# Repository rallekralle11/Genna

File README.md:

# Genna

Work in progress. I believe i can get it working but i won't deal with that right now.

Has a snap-off handle so it doesn't get stuck in a port before wires are soldered to it.
All communication pins and a few more are broken out

Licenced under CERN-OHL-P

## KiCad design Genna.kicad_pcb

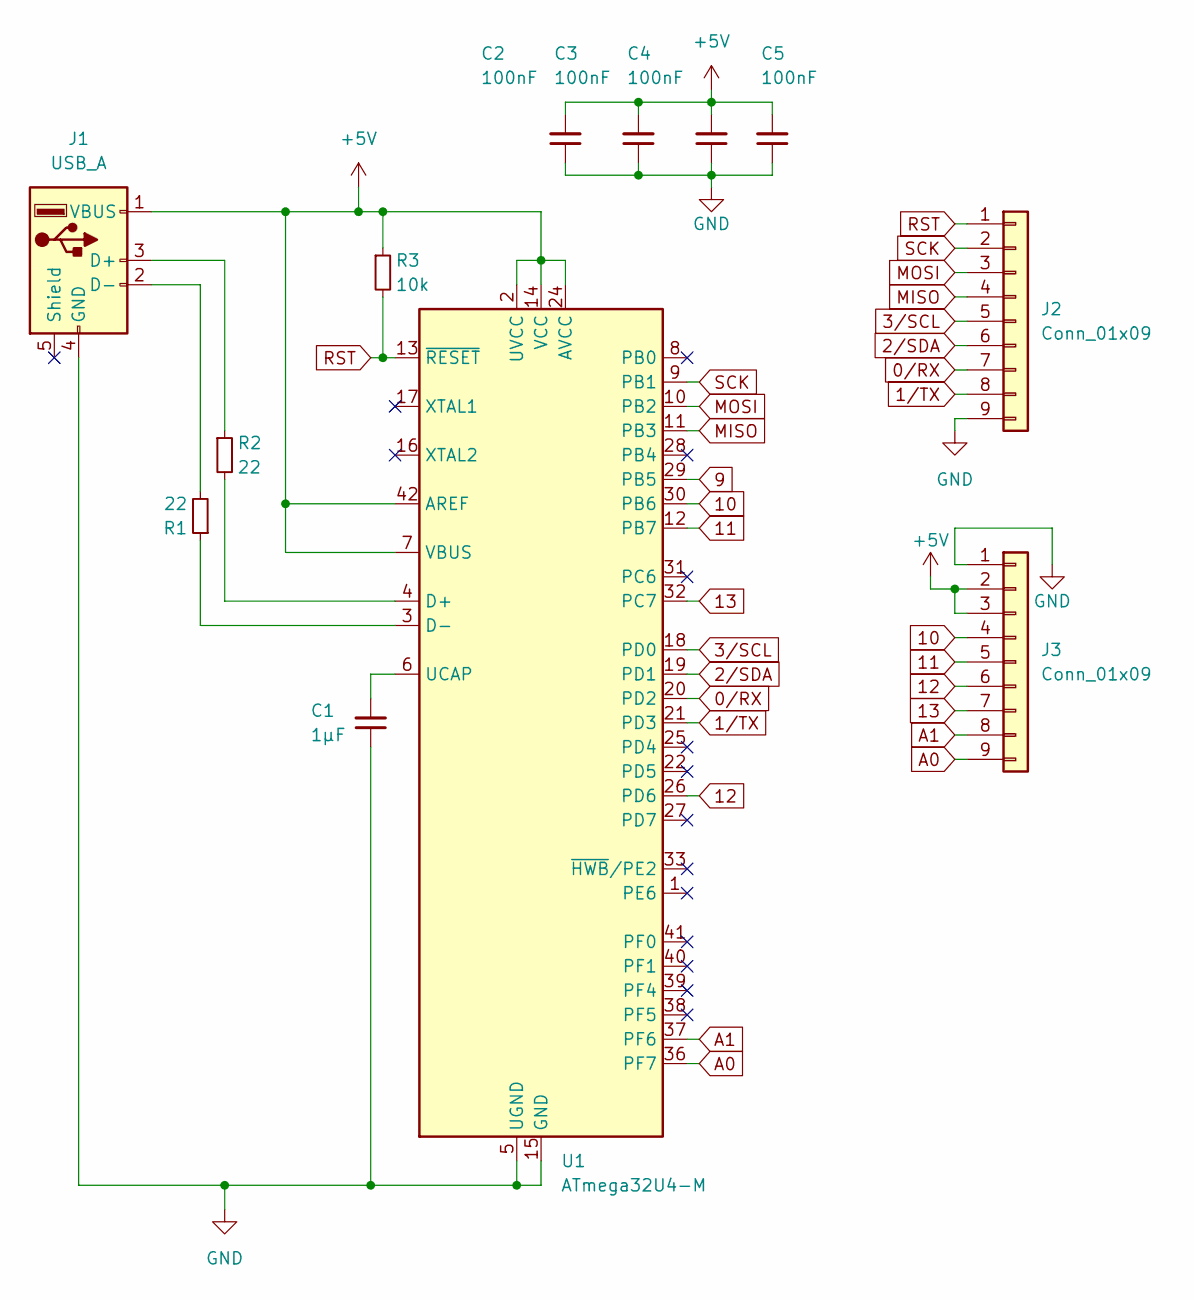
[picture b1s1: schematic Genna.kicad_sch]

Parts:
C1: 1µF; C_0402_1005Metric
C2, C3, C4, C5: 100nF; C_0402_1005Metric
J1: USB_A; USB_A_PCB_Traces
J2, J3: Conn_01x09; PinHeader_1x09_P1.27mm_Vertical
R1, R2: 22; R_0402_1005Metric
R3: 10k; R_0402_1005Metric
U1: ATmega32U4-M; QFN-44-1EP_7x7mm_P0.5mm_EP5.2x5.2mm

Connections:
0/RX: J2.7, U1.20 (PD2)
1/TX: J2.8, U1.21 (PD3)
2/SDA: J2.6, U1.19 (PD1)
3/SCL: J2.5, U1.18 (PD0)
9: U1.29 (PB5)
10: J3.4, U1.30 (PB6)
11: J3.5, U1.12 (PB7)
12: J3.6, U1.26 (PD6)
13: J3.7, U1.32 (PC7)
+5V: C2.2, C3.2, C4.2, C5.2, J1.1 (VBUS), J3.2, J3.3, R3.1, U1.2 (UVCC), U1.7 (VBUS), U1.14 (VCC), U1.24 (AVCC), U1.34 (VCC), U1.42 (AREF), U1.44 (AVCC)
A0: J3.9, U1.36 (PF7)
A1: J3.8, U1.37 (PF6)
GND: C1.1, C2.1, C3.1, C4.1, C5.1, J1.4 (GND), J2.9, J3.1, U1.5 (UGND), U1.15 (GND), U1.23 (GND), U1.35 (GND), U1.43 (GND), U1.45 (GND)
MISO: J2.4, U1.11 (PB3)
MOSI: J2.3, U1.10 (PB2)
unnamed: C1.2, U1.6 (UCAP)
unnamed: J1.2 (D-), R1.2
unnamed: J1.3 (D+), R2.1
unnamed: R1.1, U1.3 (D-)
unnamed: R2.2, U1.4 (D+)
RST: J2.1, R3.2, U1.13 (~RESET)
SCK: J2.2, U1.9 (PB1)

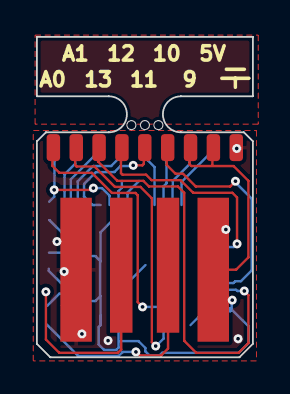
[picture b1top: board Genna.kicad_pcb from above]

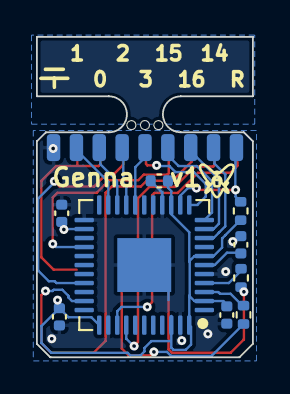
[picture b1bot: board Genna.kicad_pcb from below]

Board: 2 copper layers, 12.0 x 17.8 mm, 12 parts (10 on the bottom side), 21 nets.

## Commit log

2022-12-19 made gerbers
2022-12-19 licence
2022-12-23 changed via dimensions and had to remove an IO
